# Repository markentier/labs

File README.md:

# markentier.tech labs

**Collection of electronics/maker projects.**

* [fivebeans Coffee Notification Button](./fivebeans-cnb/README.md)

## Notes

Most code projects will use [platformIO](https://platformio.org/) setup for source code.
It shouldn't be too difficult to use them with an [Arduino IDE](https://www.arduino.cc/en/Main/Software) again if needed.
PCB designs are done with [KiCAD](http://kicad-pcb.org/).

I won't describe each project in detail, the READMEs will be pretty barebone sometimes.
Source code, schematics, layout, and Gerber files are provided as-is.

In general this repo serves mostly as a public backup and share for the interested folks.

### License and Open Source information

If not stated otherwise all files authored by me are dual-licensed under [MIT license](./LICENSE-MIT) and [Creative Commons CC-BY-SA 4.0](./LICENSE-CC); third party symbols and footprints might fall under different licenses.
KiCAD data usually uses a [Creative Commons CC-BY-SA 4.0](https://creativecommons.org/licenses/by-sa/4.0/legalcode), also read <http://kicad-pcb.org/libraries/license/> for details and exceptions/waiver.
Similar rules apply to the [DigiKey collection](https://github.com/digikey/digikey-kicad-library/).
Thus I try to use KiCAD/DigiKey libraries as much as possible.

The hardware/electronics designs are published in accordance with the [statement of principles and definition of the Open Source Hardware Association](https://www.oshwa.org/definition/).

_If you believe I violate anyone's rights or wrongly relicense their work, please contact me (open an issue) and let's find a suitable solution for all involved parties._

I use the MIT license out of habit and since it's short and unrestricted (the ISC or 0BSD might be suitable candidates as well). The CC license is used, because it seems to be widely adopted in the Open Source Hardware community, so I want to be open in that direction, too. Since I find it too cumbersome to individually declare, both source code and any other media (schematics, layouts, ...) fall under the same dual licensing, even though Creative Commons is usually not used for source code. As you might find it unsuitable (and CC itself recommends not doing it anyway), consider using the source code under the MIT license instead. No, no third option will be introduced anytime soon.

### OSHW Statement of Principles 1.0

> Open source hardware is hardware whose design is made publicly available so that anyone can study, modify, distribute, make, and sell the design or hardware based on that design. The hardware's source, the design from which it is made, is available in the preferred format for making modifications to it. Ideally, open source hardware uses readily-available components and materials, standard processes, open infrastructure, unrestricted content, and open-source design tools to maximize the ability of individuals to make and use hardware. Open source hardware gives people the freedom to control their technology while sharing knowledge and encouraging commerce through the open exchange of designs.

— <https://www.oshwa.org/definition/>

### Quote from "OSI Mission"

> Open source enables a development method for software that harnesses the power of distributed peer review and transparency of process. The promise of open source is higher quality, better reliability, greater flexibility, lower cost, and an end to predatory vendor lock-in.

— <https://opensource.org/about>

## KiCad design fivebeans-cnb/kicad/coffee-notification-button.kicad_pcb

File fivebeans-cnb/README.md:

# fivebeans Coffee Notification Button

An ESP8285 (or ESP8266) which sends a Slack message into a channel once a big button is pressed.

Show status of progress with a 24 pixel WS2812B LED ring (also known as Neopixel).

After job is done, the ESP will be turned off (so it needs an LDO with ENABLE/SHUTDOWN pin).

It's basically an overcomplicated "dash button" with fancy lights in a button and housed in a very huge case.
Funnily enough I shrunk the PCB way more than needed for the case, but I liked this challenge and wanted to get familiar with SMD soldering anyway.

## Future ideas

* use an SMD version of the ESP8266 (like ESP-12F)
* use an ESP-32 and utilize the 2 cores (main task doing all the communication + secondary task keeping the lights running concurrently)
* use an SMD ATtiny## with the ESP82## for concurrently driving the LEDs?
* _Do you have an interesting idea? Open an issue and tell me!_

The SMD ESPs would make the board bigger again, because I need to mount them somehow to the PCB, but that's okay probably. Certainly I don't want to use th bare chips and deal with antenna magic, I leave [this journey](https://www.youtube.com/watch?v=am68wkDK9UE) to the [Unexpected Maker](https://github.com/unexpectedmaker).

## Images and short videos

<small>`PCB 3D rendering for v2.1 rev1`</small>

<small>`PCB schematic rendering for v2.1 rev1`</small>

* Early prototype (Jan 2018)
  * 🎥 https://www.instagram.com/p/BefYRcdHyhK/
  * 📸 https://www.instagram.com/p/Begb8exn_ND/
* Next version on a breadboard (Feb 2019)
  * 🎥 https://www.instagram.com/p/Btrnet4omIN/
  * 📸 https://www.instagram.com/p/BtrqztWIw97/
* First self-designed PCB prototype (Feb 2019)
  * 📸 https://www.instagram.com/p/Bt_dyOYBbQA/
  * 🎥/📸 https://www.instagram.com/p/BuC8_eaBRkF/
* v2.1 rev00001 (March 2019)
  * 📸 https://www.instagram.com/p/BvDQuSpnnQZ/
  * 📸 https://www.instagram.com/p/BvFaA8wnASO/
* v2.1 rev00002 (March 2019)
  * _coming soon_

## Components

| Component  | Amount  | Notes  |
|---|---|---|
| PCB  | 1  | see kicad project  |
| ESP8285  | 1  | an ESP8266 should still work  |
| WS2812B 24 pixel ring  | 1  | RGB LEDs; so called Neopixel ring  |
| 18650 cell  | 2  | 2000mAh or better  |
| battery holder (for 2 cells)  | 1  | with a DC Jack connector  |
| wires (Dupont)  | 5  | for button and LED ring  |
| (components for PCB)  | many  | _tbd (check kicad schematic)_ |

## Frameworks

Per default the [ESP8266 Arduino framework](https://github.com/esp8266/Arduino) is used and code should be usable in their IDE.

There are other frameworks usable with ESP8266/ESP8285, but haven't done any testing yet.
Especially for JSON support one should look for a generic C/C++ library suitable for embedded devices.

### nonOS SDK

Framework: https://github.com/espressif/ESP8266_NONOS_SDK

Compatible platformio libraries: https://platformio.org/lib/search?query=framework:%22esp8266-nonos-sdk%22

### RTOS SDK

Framework: https://github.com/espressif/ESP8266_RTOS_SDK

Compatible platformio libraries: https://platformio.org/lib/search?query=framework:%22esp8266-rtos-sdk%22

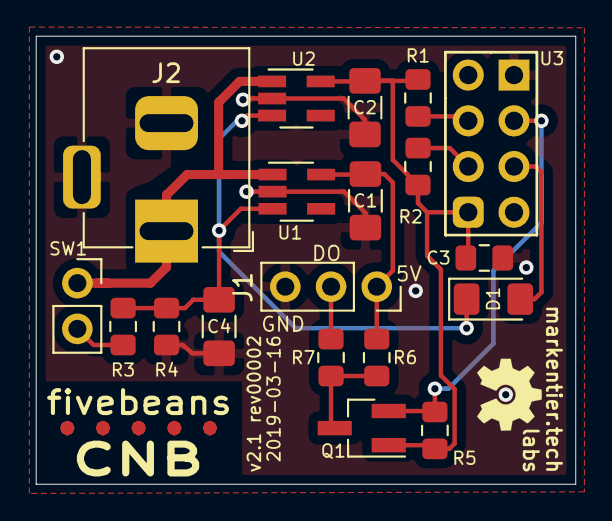
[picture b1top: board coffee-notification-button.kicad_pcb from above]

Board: 2 copper layers, 30.0 x 24.9 mm, 19 parts (0 on the bottom side), 12 nets.

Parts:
C1, C2: 2.2uF; C_1206_3216Metric_Pad1.42x1.75mm_HandSolder
C3: 1uF; C_0805_2012Metric_Pad1.15x1.40mm_HandSolder
C4: 10uF; C_1206_3216Metric_Pad1.42x1.75mm_HandSolder
D1: 1N4001; D_1206_3216Metric_Pad1.42x1.75mm_HandSolder
J1: Conn_WS2812B; PinSocket_1x03_P2.54mm_Vertical
J2: Barrel_Jack_Switch; BarrelJack_Horizontal_short-silk
Q1: FDV301N; SOT-23_Handsoldering
R1, R2, R5, R6: 10k; R_0805_2012Metric_Pad1.15x1.40mm_HandSolder
R3: 220; R_0805_2012Metric_Pad1.15x1.40mm_HandSolder
R4: 22k; R_0805_2012Metric_Pad1.15x1.40mm_HandSolder
R7: 330; R_0805_2012Metric_Pad1.15x1.40mm_HandSolder
SW1: SW_DIP_x01; PinSocket_1x02_P2.54mm_Vertical
U1: MIC5219-5.0YM5; SOT-23-5_HandSoldering
U2: MIC5219-3.3YM5; SOT-23-5_HandSoldering
U3: ESP-01 (8266 or 8285); ESP-01_no_silk_outline

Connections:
+3V3: C2.1, C3.1, Q1.1, R1.1, R2.1, R5.1, U2.5, U3.7
+5V: C1.1, J1.1, R6.1, U1.5
+BATT: J2.1, SW1.1, U1.1, U2.1
/ENABLE: C4.1, D1.1, R3.1, R4.1, U1.3, U2.3
/HOLD: D1.2, U3.6
/LED_DATA: Q1.2, R5.2, U3.4
GND: C1.2, C2.2, C3.2, C4.2, J1.3, J2.2, J2.3, R4.2, U1.2, U2.2, U3.2
unnamed: J1.2, R7.1
unnamed: Q1.3, R6.2, R7.2
unnamed: R1.2, U3.3
unnamed: R2.2, U3.5
unnamed: R3.2, SW1.2

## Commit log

2019-03-11 Add general files and folders
2019-03-11 Add fivebeans CNB project (code only)
2019-03-11 Add top level .envrc example
2019-03-12 Add images, GIF, and links to IG media
2019-03-12 Center CNB GIF in readme
2019-03-12 Try centering with more HTML
2019-03-12 Tweak image and readme for CNB
2019-03-12 Optimize PNG
2019-03-18 Add KiCAD project files
2019-03-19 Improve main readme, add lots of license voodoo
2019-03-19 Extend CNB readme
2019-03-19 Fix typo
2019-03-19 Fix image alignment

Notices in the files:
fivebeans-cnb/kicad/coffee-notification-button.kicad_pcb:
CC BY 4.0 / https://creativecommons.org/licenses/by/4.0
